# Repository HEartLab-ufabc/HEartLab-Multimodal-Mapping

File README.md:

# An Open-Source Platform for Multimodal Electrical and Optical Mapping of Ex Vivo Hearts

**A modular research platform for synchronized optical, contact-electrical, and torso-tank mapping of ex vivo perfused hearts.**

> **Repository status:** Active development. Documentation, design files, protocols, and software are being prepared for the first archived release accompanying the associated *Scientific Reports* manuscript.

## Overview

This repository contains the hardware documentation, embedded firmware, experimental-control software, CAD files, representative experimental protocols, and 3D reconstruction tools associated with the HEartLab multimodal mapping platform for ex vivo cardiac electrophysiology.

The platform integrates complementary experimental modalities within a common workflow:

- optical mapping;
- contact electrical mapping using multi-electrode arrays (MEAs);
- torso-tank electrical mapping;
- electrical stimulation;
- physiological monitoring;
- hardware synchronization;
- experiment control and event logging;
- rotational image acquisition and experiment-specific 3D reconstruction.

The system is modular rather than tied to one preparation. Perfusion interfaces, mechanical supports, electrode arrangements, optical geometry, and selected experimental procedures can be adapted according to preparation size, scientific objective, and available equipment.

---

## Experimental configurations

### Small-heart whole-organ configuration

Validated in Langendorff-perfused rabbit hearts. Depending on the experiment, the configuration supports:

- panoramic optical mapping;
- epicardial contact mapping using MEAs;
- torso-tank electrical recordings;
- programmable electrical stimulation;
- physiological monitoring;
- synchronized optical and electrical acquisition;
- experiment control and logging;
- experiment-specific 3D reconstruction.

### Large-heart whole-organ configuration

Validated in porcine and human ex vivo hearts. Depending on the experiment, the configuration supports:

- optical mapping of large cardiac surfaces;
- torso-tank electrical mapping;
- independent coronary perfusion;
- physiological monitoring;
- synchronized acquisition and stimulation;
- mechanical support adapted to larger preparations;
- experiment-specific 3D reconstruction.

### Large-heart epi-endo configuration

Developed for isolated perfused ventricular-wall preparations. Depending on the experiment, the configuration supports:

- simultaneous epicardial and endocardial optical mapping;
- paired epicardial and endocardial contact-electrical mapping;
- mirror-assisted optical access;
- coronary perfusion;
- synchronized stimulation and acquisition;
- physiological monitoring.

The configuration defines the available platform modules, while the **scientific objective determines which modules and protocols are used in a particular experiment**.

---

## Platform modules

HEartLab is organized around interoperable experimental modules:

- **Perfusion** – maintains the isolated preparation under controlled ex vivo conditions.
- **Physiological monitoring** – records perfusion flow, pressure, and temperature.
- **Optical mapping** – records voltage-sensitive fluorescence from cardiac surfaces.
- **Contact electrical mapping** – records local extracellular electrograms using MEAs.
- **Torso-tank mapping** – records cardiac potentials from electrodes surrounding the preparation in a conductive volume.
- **Electrical stimulation** – provides controlled pacing and arrhythmia-induction stimuli.
- **Hardware synchronization** – provides a common timing reference between acquisition systems.
- **Experiment control** – coordinates monitoring, stimulation, synchronization, metadata, and experimental events.
- **3D reconstruction** – combines rotational image acquisition with silhouette-based processing to obtain experiment-specific surface geometry.

---

## Repository structure

```text
HEartLab-Multimodal-Mapping/
├── README.md
├── DISCLAIMER.md
│
├── cad/
│   ├── README.md
│   ├── small_heart/
│   ├── large-heart/
│   └── epi-endo/
│
├── docs/
│   ├── getting_started.md
│   └── protocols/
│
├── firmware/
│   ├── sensors/
│   ├── gateway/
│   ├── stepper_motor_control/
│   └── synchronization_controller/
│
├── hardware/
│   ├── README.md
│   ├── BOM_overview.md
│   ├── perfusion/
│   ├── physiological_monitoring/
│   ├── optical_mapping/
│   ├── electrical_mapping/
│   ├── stimulation/
│   ├── synchronization/
│   ├── mechanical/
│   └── reconstruction_3d/
│
└── software/
    ├── README.md
    ├── experiment_control/
    ├── 3D_reconstruction_capture_labview/
    ├── 3D_reconstruction_capture_python/
    └── 3d_reconstruction_processing/
```

---

## Getting started

A high-level setup and validation workflow is provided in:

**[`docs/getting_started.md`](docs/getting_started.md)**

A typical workflow is:

1. select the experimental configuration;
2. define the scientific objective;
3. select the required platform modules and representative protocols;
4. obtain or fabricate the required hardware;
5. configure firmware and software;
6. validate each subsystem independently;
7. perform an integrated bench test;
8. document the experiment-specific configuration.

The platform does **not** require every subsystem to be used in every experiment.

---

## Experimental protocols

Representative experimental procedures are provided in:

**[`docs/protocols/`](docs/protocols/)**

These documents describe examples of HEartLab implementations rather than universal mandatory procedures. Parameters can vary according to preparation type, species or donor source, heart size, mapping modality, scientific objective, equipment, pharmacological intervention, stimulation protocol, and the applicable approved experimental protocol.

Users are responsible for confirming that concentrations, calculations, settings, and procedures are appropriate for their own experimental implementation.

---

## CAD and mechanical designs

Custom mechanical designs are provided in:

**[`cad/`](cad/)**

The CAD library is organized according to the configuration in which the components were developed:

- [`cad/small_heart/`](cad/small_heart/)
- [`cad/large-heart/`](cad/large-heart/)
- [`cad/epi-endo/`](cad/epi-endo/)

Depending on the component, files include Autodesk Inventor (`.ipt`), Autodesk Fusion (`.f3d` / `.f3z`), STEP/STP, STL, and PDF drawings.

The repository focuses on custom fabricated components. Commercial motors, bearings, pulleys, shafts, fasteners, clamps, and similar off-the-shelf parts are described in the relevant documentation rather than redistributed as proprietary CAD models.

---

## Hardware

Hardware documentation is located in:

**[`hardware/`](hardware/)**

Subsystem documentation includes:

- [`hardware/perfusion/`](hardware/perfusion/) – perfusion and fluidic hardware;
- [`hardware/physiological_monitoring/`](hardware/physiological_monitoring/) – flow, pressure, temperature, sensor nodes, and gateway hardware;
- [`hardware/optical_mapping/`](hardware/optical_mapping/) – cameras, optics, illumination, and mirror-assisted optical access;
- [`hardware/electrical_mapping/`](hardware/electrical_mapping/) – MEAs, small-heart torso-tank hardware, and large-heart tank PCB files;
- [`hardware/stimulation/`](hardware/stimulation/) – experimental constant-current stimulation hardware;
- [`hardware/synchronization/`](hardware/synchronization/) – timing and trigger-distribution hardware;
- [`hardware/mechanical/`](hardware/mechanical/) – assembly-level mechanical documentation linked to the CAD library;
- [`hardware/reconstruction_3d/`](hardware/reconstruction_3d/) – motorized rotational acquisition hardware.

A high-level component inventory is provided in [`hardware/BOM_overview.md`](hardware/BOM_overview.md).

### Large-heart tank PCB

Editable KiCad source, electrode mapping, Gerber/drill outputs, and manufacturing previews are provided under:

**[`hardware/electrical_mapping/large-heart-tank-pcb/`](hardware/electrical_mapping/large-heart-tank-pcb/)**

The large-heart tank uses six PCB faces with 15 electrode pads per face.

---

## Firmware

Embedded firmware is located in:

**[`firmware/`](firmware/)**

The current implementation includes:

- Arduino Nano-based physiological-monitoring sensor nodes;
- nRF24L01 wireless communication;
- an ESP32-S3 sensor gateway;
- a Teensy 4.1 synchronization/stimulation-control interface;
- an Arduino-controlled stepper system for rotational 3D image acquisition.

Subsystem-specific README files describe the associated interfaces and operating assumptions.

---

## Software

Software is located in:

**[`software/`](software/)**

### Experiment control

[`software/experiment_control/`](software/experiment_control/) contains the Python-based application used for experimental session organization, physiological monitoring, stimulation control, synchronization-related operations, metadata, and event logging.

### 3D image acquisition — LabVIEW / EVT

[`software/3D_reconstruction_capture_labview/`](software/3D_reconstruction_capture_labview/) contains the LabVIEW application used with the EVT camera implementation.

The acquisition workflow rotates the preparation at defined angular increments and stores the image sequence used for subsequent 3D reconstruction.

A RHYTHM-derived LabVIEW VI included in this folder retains its original third-party attribution and MIT license notice.

### 3D image acquisition — Python / Imaging Source USB

[`software/3D_reconstruction_capture_python/`](software/3D_reconstruction_capture_python/) contains the Python/OpenCV implementation used with the Imaging Source USB-camera setup.

### 3D reconstruction processing

[`software/3d_reconstruction_processing/`](software/3d_reconstruction_processing/) contains the silhouette-processing and space-carving workflow used to produce experiment-specific surface meshes.

Camera calibration is performed using [MC-Calib](https://github.com/rameau-fr/MC-Calib); its calibration procedure is not duplicated in this repository.

---

## Reproducibility and scope

The repository documents the implementation used to develop and validate the HEartLab platform. Because the platform is modular, exact equipment combinations and experimental procedures can differ among preparations.

For reproducibility, experimental records should preserve the relevant hardware configuration, firmware/software versions, acquisition settings, channel mapping, and protocol parameters used for a given dataset.

Commercial acquisition software, manufacturer drivers, SDKs, and proprietary third-party design files are not redistributed unless their licenses permit redistribution.

---

## Associated manuscript

This repository accompanies:

**Silva, V. P. et al. _An Open-Source Platform for Multimodal Electrical and Optical Mapping of Ex Vivo Hearts_.**

**Status:** manuscript under review.

---

## License

This repository uses a **multi-license structure**:

| Material | License |
|---|---|
| Original software and firmware | MIT License |
| Original hardware and CAD designs | CERN Open Hardware Licence Version 2 – Permissive |
| General documentation and experimental protocols | Creative Commons Attribution 4.0 International |
| Third-party components | Original third-party licenses |

See [`LICENSE.md`](LICENSE.md) for the complete scope and
[`THIRD_PARTY.md`](THIRD_PARTY.md) for third-party exceptions.

---

## Third-party components

Third-party software remains subject to its original license terms.

In particular, the LabVIEW reconstruction-acquisition folder contains a VI derived from the RHYTHM open-source imaging toolkit. Attribution and the applicable MIT license notice are provided in:

[`software/3D_reconstruction_capture_labview/THIRD_PARTY.md`](software/3D_reconstruction_capture_labview/THIRD_PARTY.md)

---

## Contact

For technical questions or reproducibility issues, please open a GitHub issue.

For research collaboration or questions regarding the associated manuscript, contact HEartLab at Universidade Federal do ABC (UFABC).

---

## Disclaimer

The hardware designs, firmware, software, protocols, CAD files, and documentation provided in this repository are supplied **"as is"**, without warranties or guarantees of any kind, either express or implied.

The materials are intended exclusively for experimental research involving ex vivo cardiac preparations. They have not been designed, validated, or approved as medical devices and must not be used for clinical diagnosis, treatment, patient monitoring, or direct use in humans.

Users are responsible for independently reviewing and validating hardware, software, calculations, procedures, electrical connections, experimental parameters, concentrations, and safety measures before use.

The individual researcher or institution conducting an experiment remains responsible for determining whether the platform and associated procedures are appropriate for the intended application and for ensuring compliance with applicable ethical approvals, institutional requirements, laboratory procedures, and safety regulations.

See the complete [`DISCLAIMER.md`](DISCLAIMER.md).

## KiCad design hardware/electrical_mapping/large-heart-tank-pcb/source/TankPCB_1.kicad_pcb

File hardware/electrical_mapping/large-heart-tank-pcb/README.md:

# Large-Heart Tank Electrode PCB

This directory contains the KiCad design and manufacturing files for the custom electrode PCB used on the large-heart torso-tank mapping system.

The PCB forms one face of the large-heart tank electrode assembly.

## Tank arrangement

The large-heart whole-organ tank uses:

- six PCB faces;
- 15 electrode pads per PCB;
- 90 bath-potential electrodes when all six faces are populated.

The custom mechanical support for these boards is documented at:

[`../../../cad/large-heart/transparent-pcb-support/`](../../../cad/large-heart/transparent-pcb-support/)

## Current PCB design

The uploaded design contains:

- 15 circular electrode pads;
- one 1×16, 2.54 mm pitch horizontal pin-header footprint;
- one-to-one connections from electrode pads `U1`–`U15` to connector pins `1`–`15`;
- connector pin `16` with no corresponding electrode pad in the current PCB project;
- a custom `Round_Pad` footprint with a nominal 10 mm circular copper pad.

See:

[`electrode_mapping.csv`](electrode_mapping.csv)

## Board outline

The current KiCad edge-cuts geometry spans approximately:

- 303 mm in X;
- 115 mm in Y;

including the connector-tab region.

## Directory structure

```text
large-heart-tank-pcb/
├── README.md
├── electrode_mapping.csv
├── source/
├── manufacturing/
│   ├── README.md
│   ├── gerbers/
│   ├── drill/
│   └── TankPCB_manufacturing.zip
└── previews/
```

## Source files

[`source/`](source/) contains only the files needed to reopen and edit the KiCad project:

- KiCad project;
- schematic;
- PCB layout;
- project-local symbol library;
- project-local footprint library;
- library tables.

## Manufacturing files

[`manufacturing/`](manufacturing/) contains the Gerber and drill outputs from the supplied project.

The provided manufacturing archive should be checked in a Gerber viewer before fabrication.

## Important: PCB material

> [!WARNING]
> The current `TankPCB_1.kicad_pcb` file declares a conventional 1.6 mm FR4 stack-up. This happens because KiCAD does not offer PET as manufacturing material. When ordering your board from your preferred manufacturer check their constraints and preferred file format.

## Electrode finish

The KiCad/Gerber design defines the copper geometry but does not fully document any post-fabrication electrode plating or surface treatment.

Order the surface finish as "immersion silver (Ag)" or the manufacturer equivalent.

## Connector

The current design uses a 1×16, 2.54 mm pitch horizontal header footprint.

Pins 1–15 connect to the 15 electrode pads. Pin 16 does not have a corresponding round electrode in the current board layout.

Be very careful while soldering the pins, the transparent PCB material is generally extremely sensitive to high heat.

## KiCad version

The supplied PCB file was generated by KiCad 9.0.

The custom symbol/footprint libraries are included locally.

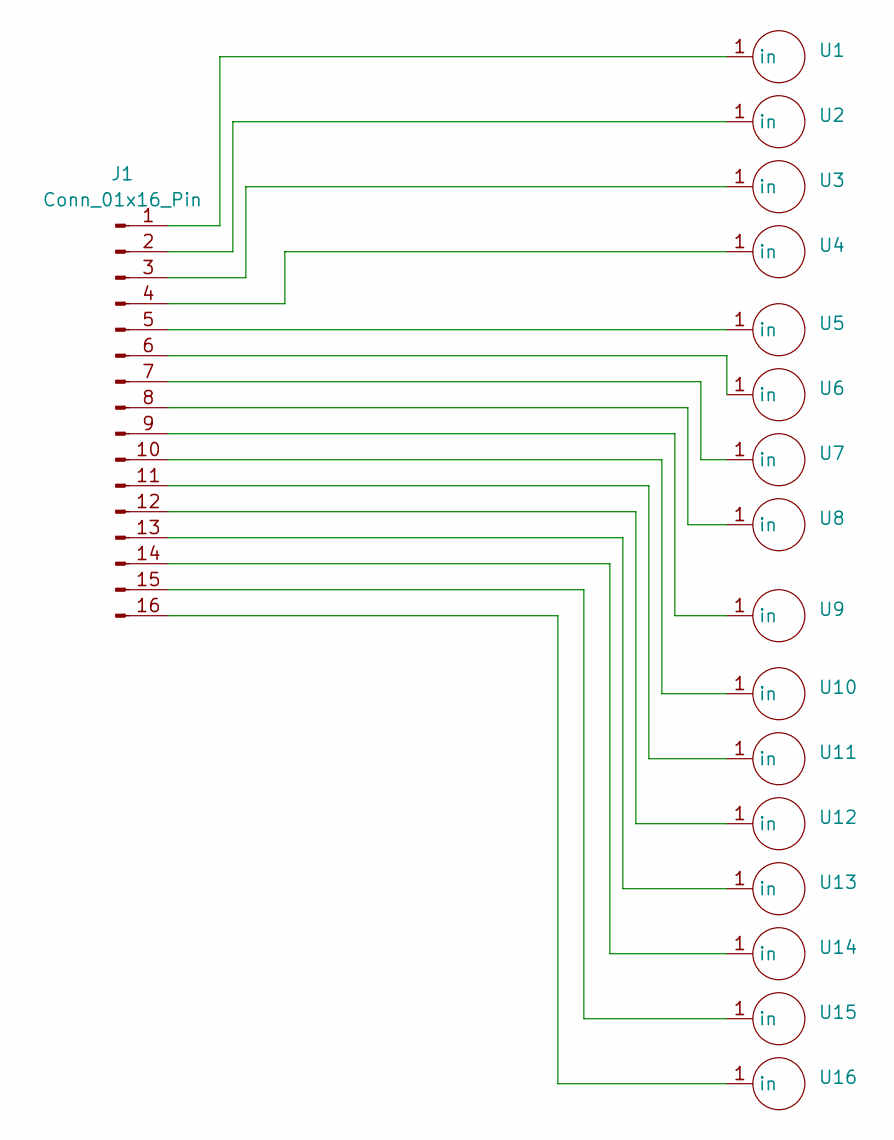
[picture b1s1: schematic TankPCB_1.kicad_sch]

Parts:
J1: Conn_01x16_Pin; PinHeader_1x16_P2.54mm_Horizontal
U1, U2, U3, U4, U5, U6, U7, U8, U9, U10, U11, U12, U13, U14, U15, U16: Round_Pad

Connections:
unnamed: J1.1, U1.1 (in)
unnamed: J1.2, U2.1 (in)
unnamed: J1.3, U3.1 (in)
unnamed: J1.4, U4.1 (in)
unnamed: J1.5, U5.1 (in)
unnamed: J1.6, U6.1 (in)
unnamed: J1.7, U7.1 (in)
unnamed: J1.8, U8.1 (in)
unnamed: J1.9, U9.1 (in)
unnamed: J1.10, U10.1 (in)
unnamed: J1.11, U11.1 (in)
unnamed: J1.12, U12.1 (in)
unnamed: J1.13, U13.1 (in)
unnamed: J1.14, U14.1 (in)
unnamed: J1.15, U15.1 (in)
unnamed: J1.16, U16.1

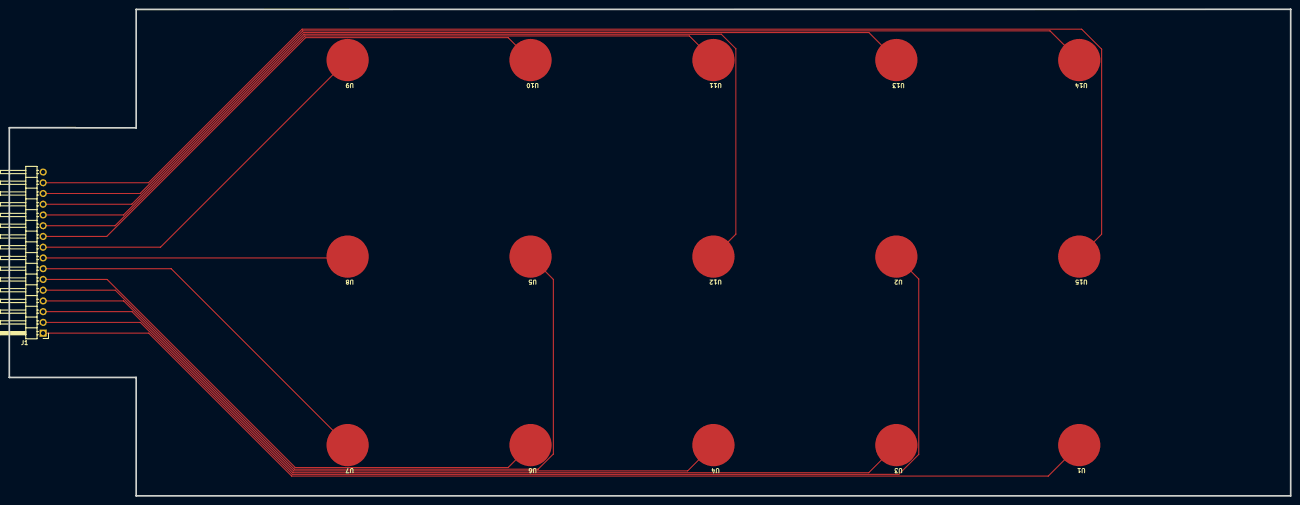
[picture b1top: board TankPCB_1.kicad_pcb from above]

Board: 2 copper layers, 303.0 x 115.0 mm, 16 parts (0 on the bottom side), 15 nets.
